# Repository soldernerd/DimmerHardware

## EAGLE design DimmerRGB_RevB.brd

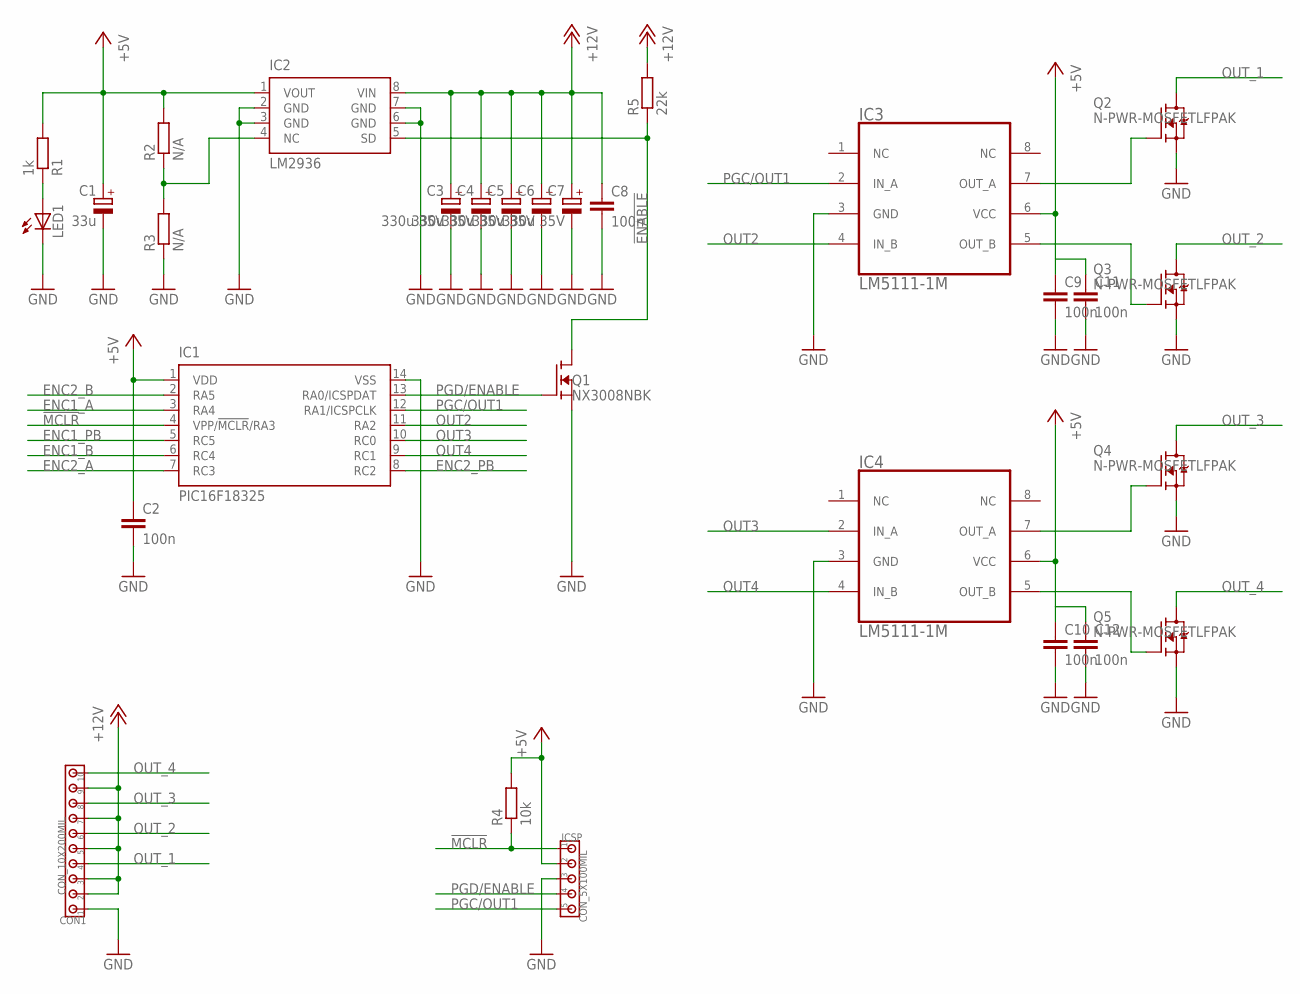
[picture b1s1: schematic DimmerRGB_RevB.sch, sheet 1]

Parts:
C1: 33u; SMC_C
C2, C8, C9, C10, C11, C12: 100n; C0805
C3, C4, C5, C6, C7: 330u 35V; 10MM
CON1: CON_10X200MIL; 200MIL_10X
IC1: PIC16F18325; SO14
IC2: LM2936; SOIC8
IC3, IC4: LM5111-1M; SOIC8
ICSP: CON_5X100MIL; 100MIL_5X
LED1: LED0805
Q1: NX3008NBK; SOT23
Q2, Q3, Q4, Q5: N-PWR-MOSFETLFPAK; LFPAK
R1: 1k; R0805
R2, R3: N/A; R0805
R4: 10k; R0805
R5: 22k; R0805

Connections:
!ENABLE!: IC2.5 (SD), Q1.3 (D), R5.1; also elsewhere on the board
!MCLR!: IC1.4 (VPP/!MCLR!/RA3), ICSP.1, R4.1
+5V: C1.+, C2.1, C9.1, C10.1, C11.1, C12.1, IC1.1 (VDD), IC2.1 (VOUT), IC3.6 (VCC), IC4.6 (VCC), ICSP.2, R1.2, R2.2, R4.2; also elsewhere on the board
+12V: C3.+, C4.+, C5.+, C6.+, C7.+, C8.1, CON1.2, CON1.3, CON1.5, CON1.7, CON1.9, IC2.8 (VIN), R5.2
ENC1_A: IC1.3 (RA4); also elsewhere on the board
ENC1_B: IC1.6 (RC4); also elsewhere on the board
ENC1_PB: IC1.5 (RC5); also elsewhere on the board
ENC2_A: IC1.7 (RC3); also elsewhere on the board
ENC2_B: IC1.2 (RA5); also elsewhere on the board
ENC2_PB: IC1.8 (RC2); also elsewhere on the board
GND: C1.-, C2.2, C3.-, C4.-, C5.-, C6.-, C7.-, C8.2, C9.2, C10.2, C11.2, C12.2, CON1.1, IC1.14 (VSS), IC2.2 (GND), IC2.3 (GND), IC2.6 (GND), IC2.7 (GND), IC3.3 (GND), IC4.3 (GND), ICSP.3, LED1.C, Q1.2 (S), Q2.1 (S), Q2.2 (S), Q2.3 (S), Q3.1 (S), Q3.2 (S), Q3.3 (S), Q4.1 (S), Q4.2 (S), Q4.3 (S), Q5.1 (S), Q5.2 (S), Q5.3 (S), R3.1; also elsewhere on the board
unnamed: IC4.5 (OUT_B), Q5.4 (G)
unnamed: LED1.A, R1.1
unnamed: IC3.7 (OUT_A), Q2.4 (G)
unnamed: IC4.7 (OUT_A), Q4.4 (G)
unnamed: IC2.4 (NC), R2.1, R3.2
unnamed: IC3.5 (OUT_B), Q3.4 (G)
OUT2: IC1.11 (RA2), IC3.4 (IN_B)
OUT3: IC1.10 (RC0), IC4.2 (IN_A)
OUT4: IC1.9 (RC1), IC4.4 (IN_B)
OUT_1: CON1.4, Q2.MB1 (D), Q2.MB2 (D), Q2.MB3 (D), Q2.VIA1 (D), Q2.VIA2 (D), Q2.VIA3 (D), Q2.VIA4 (D), Q2.VIA5 (D), Q2.VIA6 (D), Q2.VIA7 (D), Q2.VIA8 (D), Q2.VIA9 (D)
OUT_2: CON1.6, Q3.MB1 (D), Q3.MB2 (D), Q3.MB3 (D), Q3.VIA1 (D), Q3.VIA2 (D), Q3.VIA3 (D), Q3.VIA4 (D), Q3.VIA5 (D), Q3.VIA6 (D), Q3.VIA7 (D), Q3.VIA8 (D), Q3.VIA9 (D)
OUT_3: CON1.8, Q4.MB1 (D), Q4.MB2 (D), Q4.MB3 (D), Q4.VIA1 (D), Q4.VIA2 (D), Q4.VIA3 (D), Q4.VIA4 (D), Q4.VIA5 (D), Q4.VIA6 (D), Q4.VIA7 (D), Q4.VIA8 (D), Q4.VIA9 (D)
OUT_4: CON1.10, Q5.MB1 (D), Q5.MB2 (D), Q5.MB3 (D), Q5.VIA1 (D), Q5.VIA2 (D), Q5.VIA3 (D), Q5.VIA4 (D), Q5.VIA5 (D), Q5.VIA6 (D), Q5.VIA7 (D), Q5.VIA8 (D), Q5.VIA9 (D)
PGC/OUT1: IC1.12 (RA1/ICSPCLK), IC3.2 (IN_A), ICSP.5
PGD/ENABLE: IC1.13 (RA0/ICSPDAT), ICSP.4, Q1.1 (G)

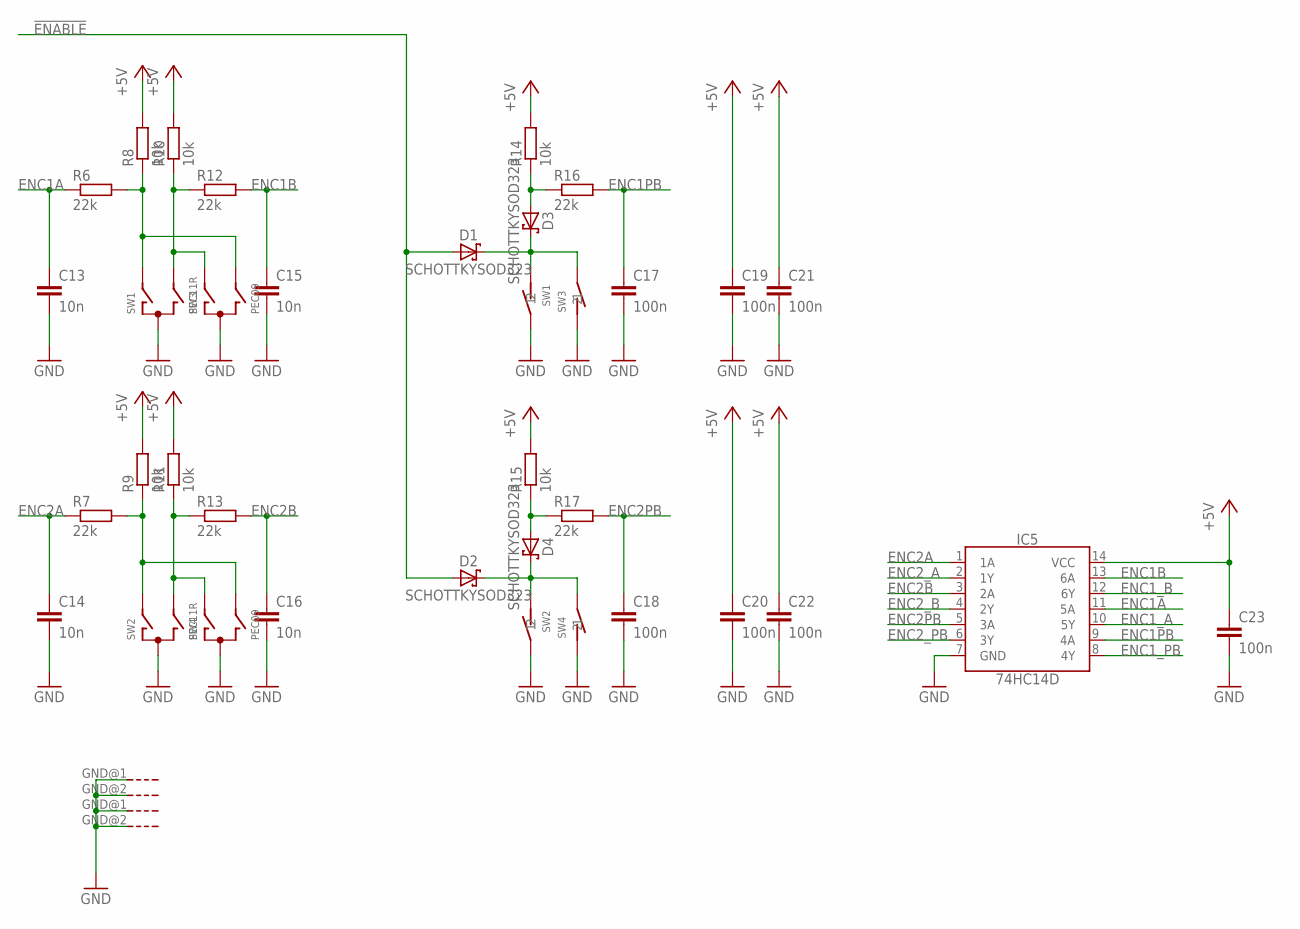
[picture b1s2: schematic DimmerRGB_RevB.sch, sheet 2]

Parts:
C13, C14, C15, C16: 10n; C0805
C17, C18, C19, C20, C21, C22, C23: 100n; C0805
D1, D2, D3, D4: SCHOTTKYSOD323; SOD323
IC5: 74HC14D; SO14
R6, R7, R12, R13, R16, R17: 22k; R0805
R8, R9, R10, R11, R14, R15: 10k; R0805
SW1, SW2: PEC11R; ENCODER_BOURNS
SW3, SW4: PEC09

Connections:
!ENABLE!: D1.A, D2.A; also elsewhere on the board
+5V: C19.1, C20.1, C21.1, C22.1, C23.1, IC5.14 (VCC), R8.2, R9.2, R10.2, R11.2, R14.2, R15.2; also elsewhere on the board
ENC1A: C13.1, IC5.11 (5A), R6.1
ENC1B: C15.1, IC5.13 (6A), R12.2
ENC1PB: C17.1, IC5.9 (4A), R16.2
ENC1_A: IC5.10 (5Y); also elsewhere on the board
ENC1_B: IC5.12 (6Y); also elsewhere on the board
ENC1_PB: IC5.8 (4Y); also elsewhere on the board
ENC2A: C14.1, IC5.1 (1A), R7.1
ENC2B: C16.1, IC5.3 (2A), R13.2
ENC2PB: C18.1, IC5.5 (3A), R17.2
ENC2_A: IC5.2 (1Y); also elsewhere on the board
ENC2_B: IC5.4 (2Y); also elsewhere on the board
ENC2_PB: IC5.6 (3Y); also elsewhere on the board
GND: C13.2, C14.2, C15.2, C16.2, C17.2, C18.2, C19.2, C20.2, C21.2, C22.2, C23.2, IC5.7 (GND), SW1.2, SW1.C, SW1.GND@1 (G), SW1.GND@2 (G), SW2.2, SW2.C, SW2.GND@1 (G), SW2.GND@2 (G), SW3.C, SW3.D (1), SW4.C, SW4.D (1); also elsewhere on the board
unnamed: D2.C, D4.C, SW2.1, SW4.E (2)
unnamed: R10.1, R12.1, SW1.B, SW3.A
unnamed: R6.2, R8.1, SW1.A, SW3.B
unnamed: D3.A, R14.1, R16.1
unnamed: R7.2, R9.1, SW2.A, SW4.B
unnamed: D4.A, R15.1, R17.1
unnamed: D1.C, D3.C, SW1.1, SW3.E (2)
unnamed: R11.1, R13.1, SW2.B, SW4.A

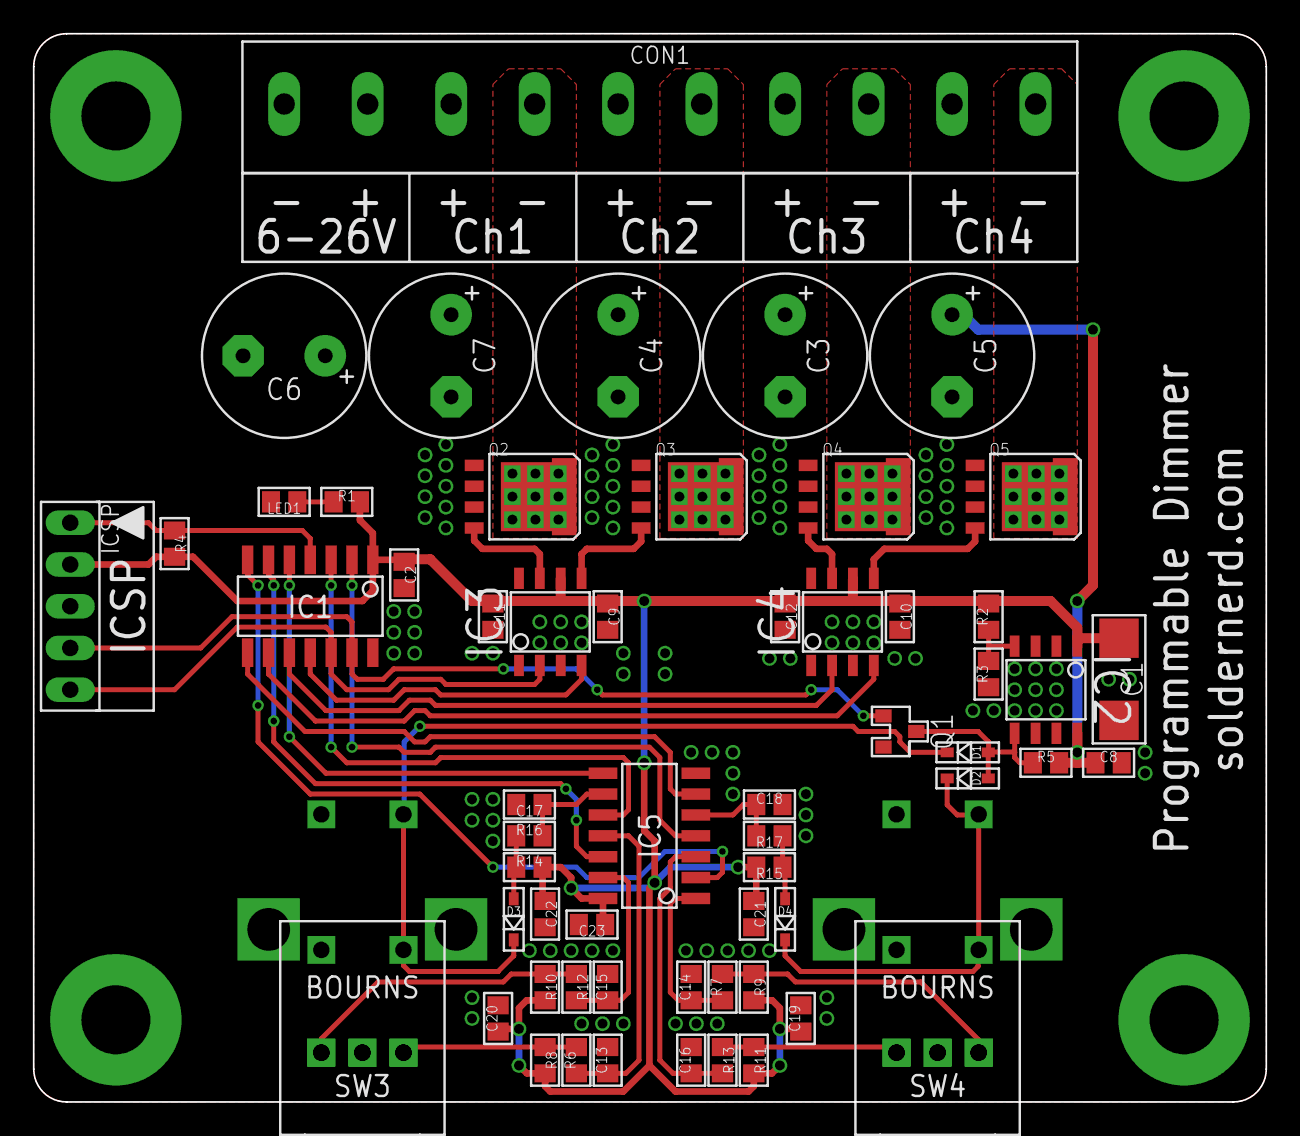
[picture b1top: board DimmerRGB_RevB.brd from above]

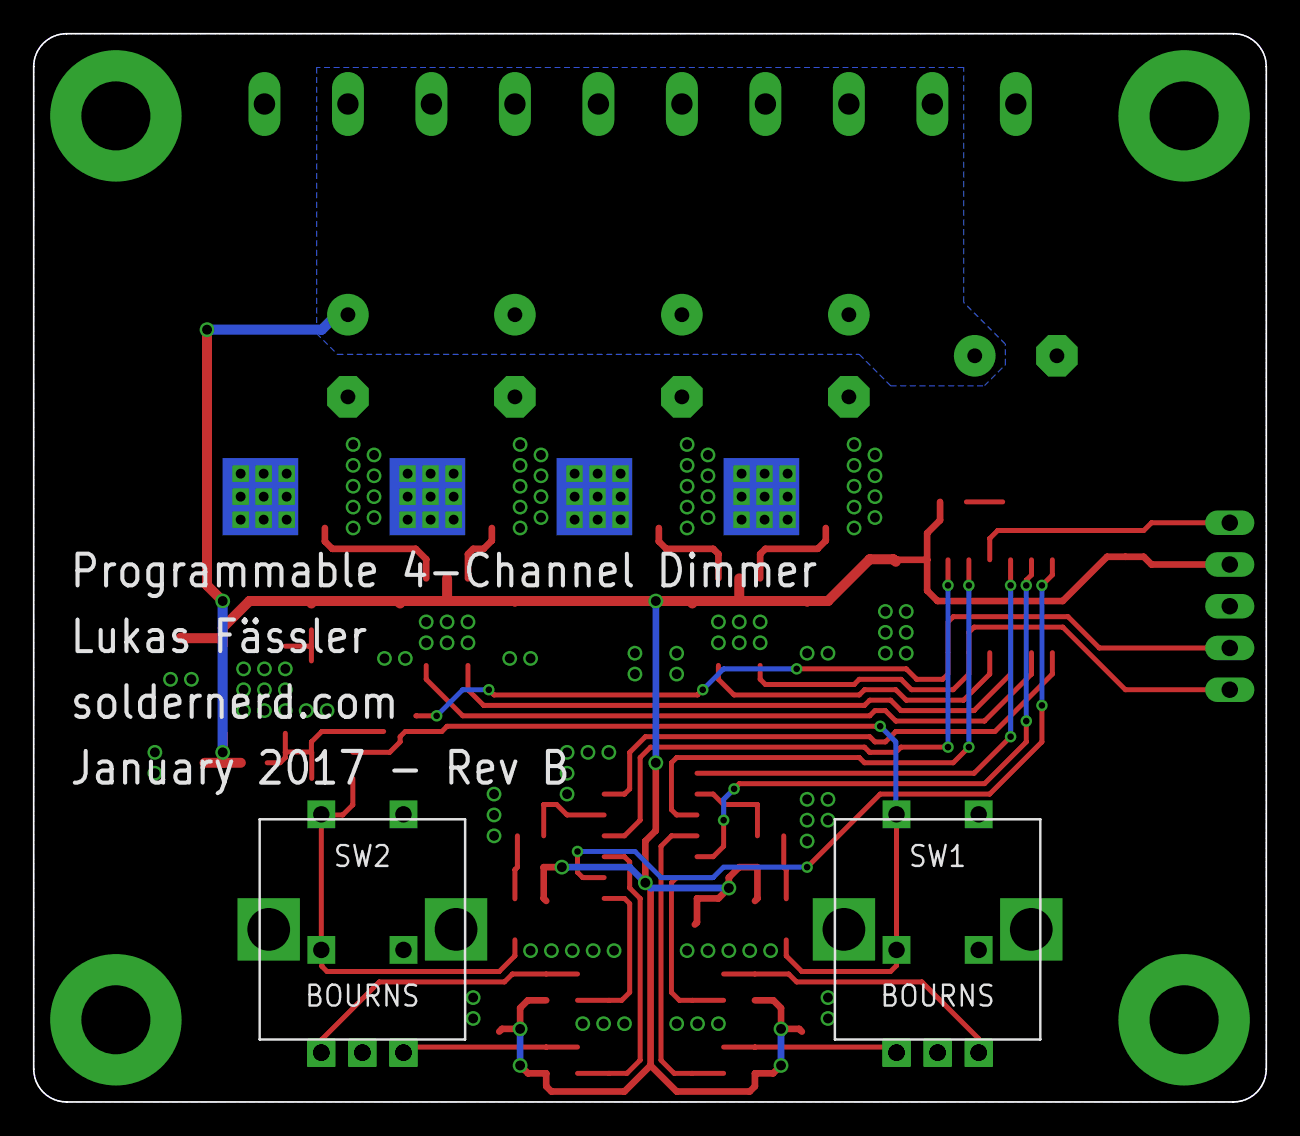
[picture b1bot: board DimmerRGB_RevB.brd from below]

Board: 2 copper layers, 75.0 x 65.0 mm, 61 parts (2 on the bottom side), 40 nets.

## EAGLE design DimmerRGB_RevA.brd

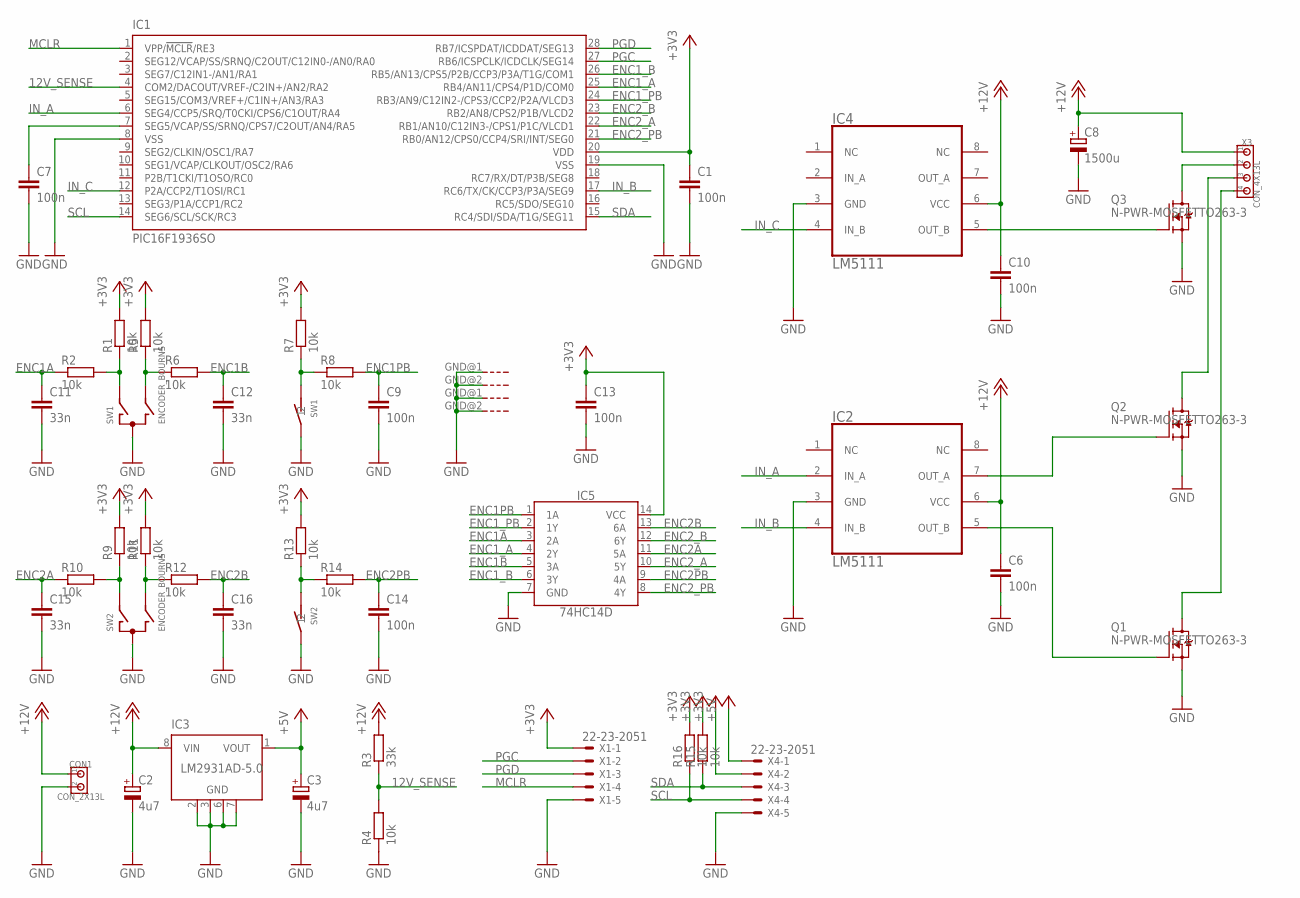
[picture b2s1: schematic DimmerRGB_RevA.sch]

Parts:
C1, C6, C7, C9, C10, C13, C14: 100n; C0805
C2, C3: 4u7; SMC_C
C8: 1500u; 10MM
C11, C12, C15, C16: 33n; C0805
CON1: CON_2X13L; 200MIL_2X
IC1: PIC16F1936SO; SO28W
IC2, IC4: LM5111; SOIC8
IC3: LM2931AD-5.0; SO8
IC5: 74HC14D; SO14
Q1, Q2, Q3: N-PWR-MOSFETTO263-3; TO263-3
R1, R2, R4, R5, R6, R7, R8, R9, R10, R11, R12, R13, R14, R15, R16: 10k; R0805
R3: 33k; R0805
SW1, SW2: ENCODER_BOURNS
X1, X4: 22-23-2051
X3: CON_4X13L; 200MIL_4X

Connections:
12V_SENSE: IC1.4 (COM2/DACOUT/VREF-/C2IN+/AN2/RA2), R3.1, R4.2
+3V3: C1.1, C13.1, IC1.20 (VDD), IC5.14 (VCC), R1.2, R5.2, R7.2, R9.2, R11.2, R13.2, R15.2, R16.2, X1.1, X4.2
+5V: C3.+, IC3.1 (VOUT), X4.1
+12V: C2.+, C6.1, C8.+, C10.1, CON1.1, IC2.6 (VCC), IC3.8 (VIN), IC4.6 (VCC), R3.2, X3.1
ENC1A: C11.1, IC5.3 (2A), R2.1
ENC1B: C12.1, IC5.5 (3A), R6.2
ENC1PB: C9.1, IC5.1 (1A), R8.2
ENC1_A: IC1.25 (RB4/AN11/CPS4/P1D/COM0), IC5.4 (2Y)
ENC1_B: IC1.26 (RB5/AN13/CPS5/P2B/CCP3/P3A/T1G/COM1), IC5.6 (3Y)
ENC1_PB: IC1.24 (RB3/AN9/C12IN2-/CPS3/CCP2/P2A/VLCD3), IC5.2 (1Y)
ENC2A: C15.1, IC5.11 (5A), R10.1
ENC2B: C16.1, IC5.13 (6A), R12.2
ENC2PB: C14.1, IC5.9 (4A), R14.2
ENC2_A: IC1.22 (RB1/AN10/C12IN3-/CPS1/P1C/VLCD1), IC5.10 (5Y)
ENC2_B: IC1.23 (RB2/AN8/CPS2/P1B/VLCD2), IC5.12 (6Y)
ENC2_PB: IC1.21 (RB0/AN12/CPS0/CCP4/SRI/INT/SEG0), IC5.8 (4Y)
GND: C1.2, C2.-, C3.-, C6.2, C7.2, C8.-, C9.2, C10.2, C11.2, C12.2, C13.2, C14.2, C15.2, C16.2, CON1.2, IC1.8 (VSS), IC1.19 (VSS), IC2.3 (GND), IC3.2 (GND), IC3.3 (GND), IC3.6 (GND), IC3.7 (GND), IC4.3 (GND), IC5.7 (GND), Q1.3 (S), Q2.3 (S), Q3.3 (S), R4.1, SW1.2, SW1.C, SW1.GND@1 (G), SW1.GND@2 (G), SW2.2, SW2.C, SW2.GND@1 (G), SW2.GND@2 (G), X1.5, X4.5
IN_A: IC1.6 (SEG4/CCP5/SRQ/T0CKI/CPS6/C1OUT/RA4), IC2.2 (IN_A)
IN_B: IC1.17 (RC6/TX/CK/CCP3/P3A/SEG9), IC2.4 (IN_B)
IN_C: IC1.12 (P2A/CCP2/T1OSI/RC1), IC4.4 (IN_B)
MCLR: IC1.1 (VPP/!MCLR!/RE3), X1.4
unnamed: IC2.5 (OUT_B), Q1.1 (G)
unnamed: Q1.TAB (D), X3.4
unnamed: Q2.TAB (D), X3.3
unnamed: C7.1, IC1.7 (SEG5/VCAP/SS/SRNQ/CPS7/C2OUT/AN4/RA5)
unnamed: IC2.7 (OUT_A), Q2.1 (G)
unnamed: IC4.5 (OUT_B), Q3.1 (G)
unnamed: Q3.TAB (D), X3.2
unnamed: R5.1, R6.1, SW1.B
unnamed: R1.1, R2.2, SW1.A
unnamed: R7.1, R8.1, SW1.1
unnamed: R11.1, R12.1, SW2.B
unnamed: R9.1, R10.2, SW2.A
unnamed: R13.1, R14.1, SW2.1
PGC: IC1.27 (RB6/ICSPCLK/ICDCLK/SEG14), X1.2
PGD: IC1.28 (RB7/ICSPDAT/ICDDAT/SEG13), X1.3
SCL: IC1.14 (SEG6/SCL/SCK/RC3), R16.1, X4.4
SDA: IC1.15 (RC4/SDI/SDA/T1G/SEG11), R15.1, X4.3

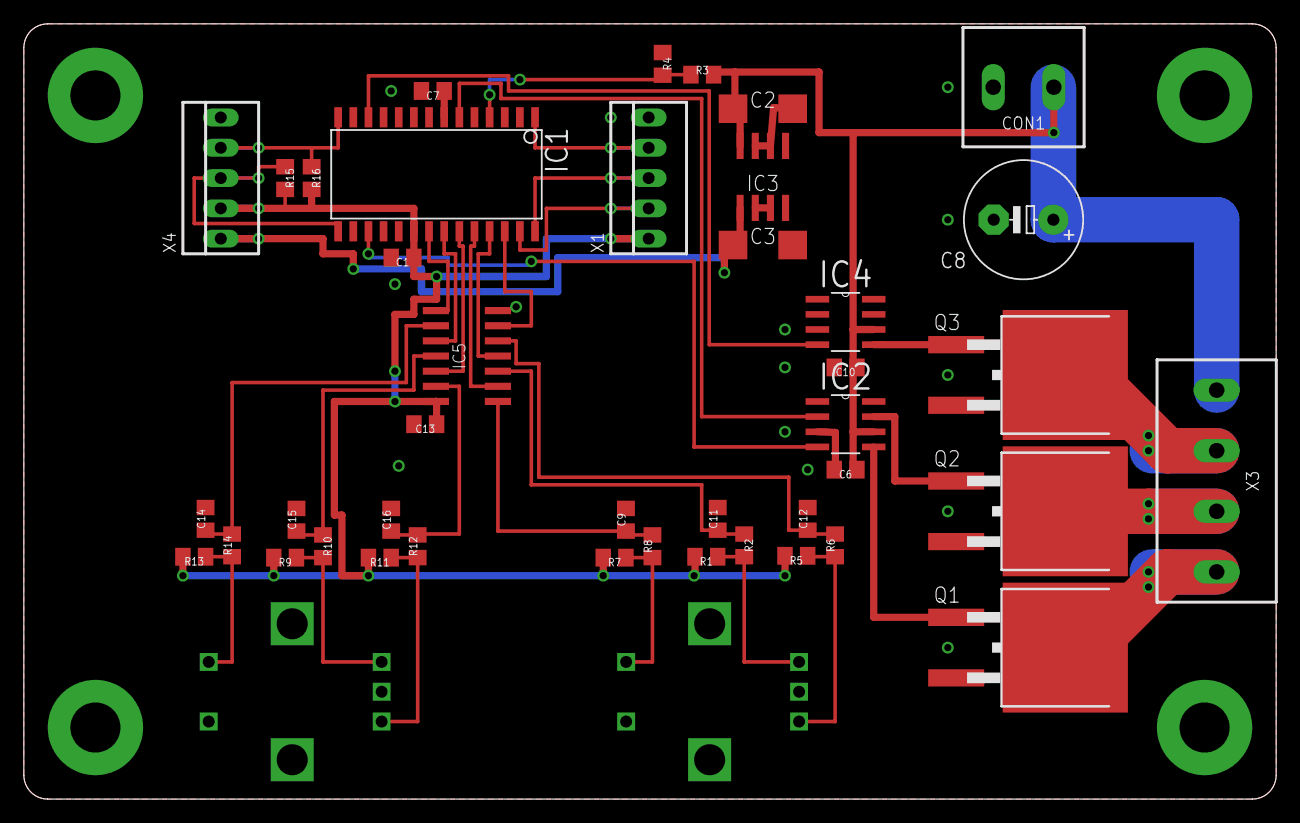
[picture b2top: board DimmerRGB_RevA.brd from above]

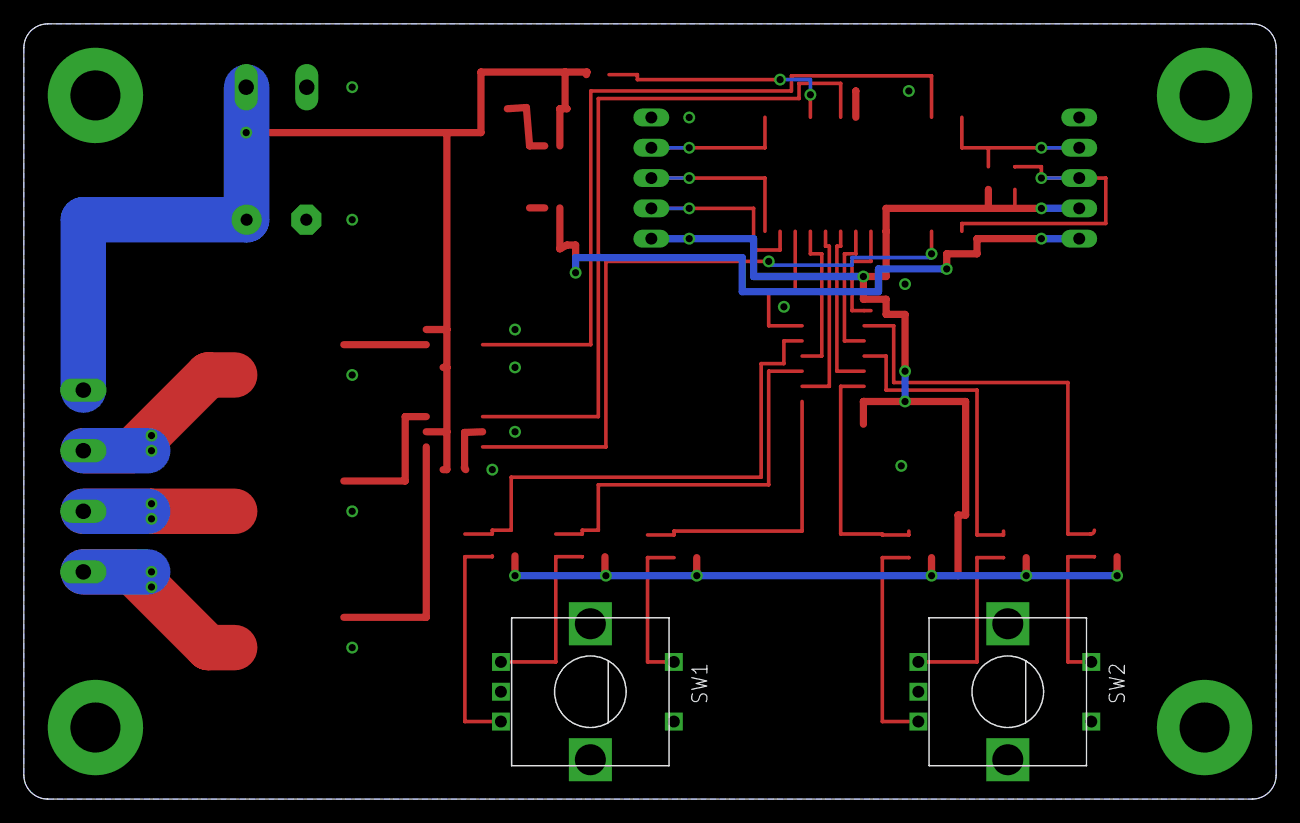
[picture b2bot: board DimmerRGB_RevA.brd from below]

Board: 2 copper layers, 105.0 x 65.0 mm, 44 parts (2 on the bottom side), 38 nets.

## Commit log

2017-01-07 .gitignore added
2017-01-09 Worked on RBG RevB layout
2017-01-10 Some more layouting done
2017-01-13 More layouting done
2017-02-03 Final version of RGB dimmer Rev B
2017-03-18 Linear regulator changed
